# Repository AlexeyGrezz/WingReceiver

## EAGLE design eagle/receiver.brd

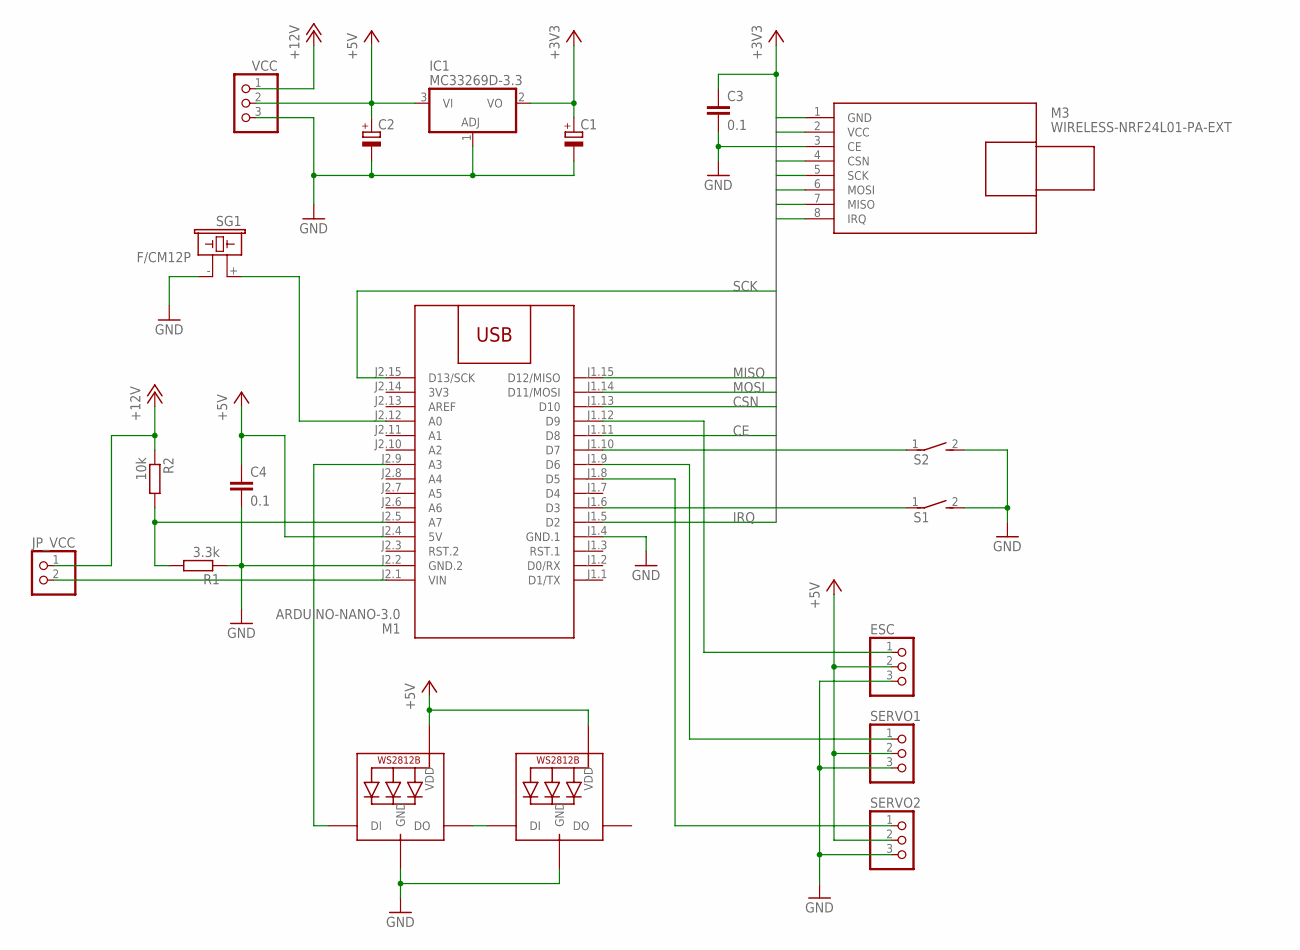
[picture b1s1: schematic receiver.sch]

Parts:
C1, C2: CPOL-EUE3.5-8; E3,5-8
C3, C4: 0.1; C050-024X044
ESC: PINHD-1X3; 1X03
IC1: MC33269D-3.3; DPACK
JP_VCC: PINHD-1X2; 1X02
LED1, LED2: WS2812B_5050N; WS2812B-NARROW
M1: ARDUINO-NANO-3.0
M3: WIRELESS-NRF24L01-PA-EXT; WIRELESS-NRD24L01-PA-EXT
R1: 3.3k; 0207/10
R2: 10k; 0207/10
S1, S2: DS01E; DS-01
SERVO1, SERVO2: PINHD-1X3; 1X03
SG1: F/CM12P
VCC: PINHD-1X3; 1X03

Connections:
3V3: M1.J2.14 (3V3)
+3V3: C1.+, C3.1, IC1.2 (VO), M3.2 (VCC)
+5V: C2.+, C4.1, ESC.2, IC1.3 (VI), LED1.1-VDD (VDD), LED2.1-VDD (VDD), M1.J2.4 (5V), SERVO1.2, SERVO2.2, VCC.2
+12V: JP_VCC.1, R2.1, VCC.1
CE: M1.J1.11 (D8), M3.3 (CE)
CSN: M1.J1.13 (D10), M3.4 (CSN)
GND: C1.-, C2.-, C3.2, C4.2, ESC.3, IC1.1 (ADJ), LED1.3-GND (GND), LED2.3-GND (GND), M1.J1.4 (GND.1), M1.J2.2 (GND.2), M3.1 (GND), R1.1, S1.2, S2.2, SERVO1.3, SERVO2.3, SG1.- (2), VCC.3
IRQ: M1.J1.5 (D2), M3.8 (IRQ)
MISO: M1.J1.15 (D12/MISO), M3.7 (MISO)
MOSI: M1.J1.14 (D11/MOSI), M3.6 (MOSI)
unnamed: ESC.1, M1.J1.12 (D9)
unnamed: M1.J1.9 (D6), SERVO1.1
unnamed: M1.J1.8 (D5), SERVO2.1
unnamed: JP_VCC.2, M1.J2.1 (VIN)
unnamed: M1.J2.5 (A7), R1.2, R2.2
unnamed: LED1.2-DOUT (DO), LED2.4-DIN (DI)
unnamed: M1.J2.12 (A0), SG1.+ (1)
unnamed: LED1.4-DIN (DI), M1.J2.9 (A3)
unnamed: M1.J1.6 (D3), S1.1
unnamed: M1.J1.10 (D7), S2.1
SCK: M1.J2.15 (D13/SCK), M3.5 (SCK)

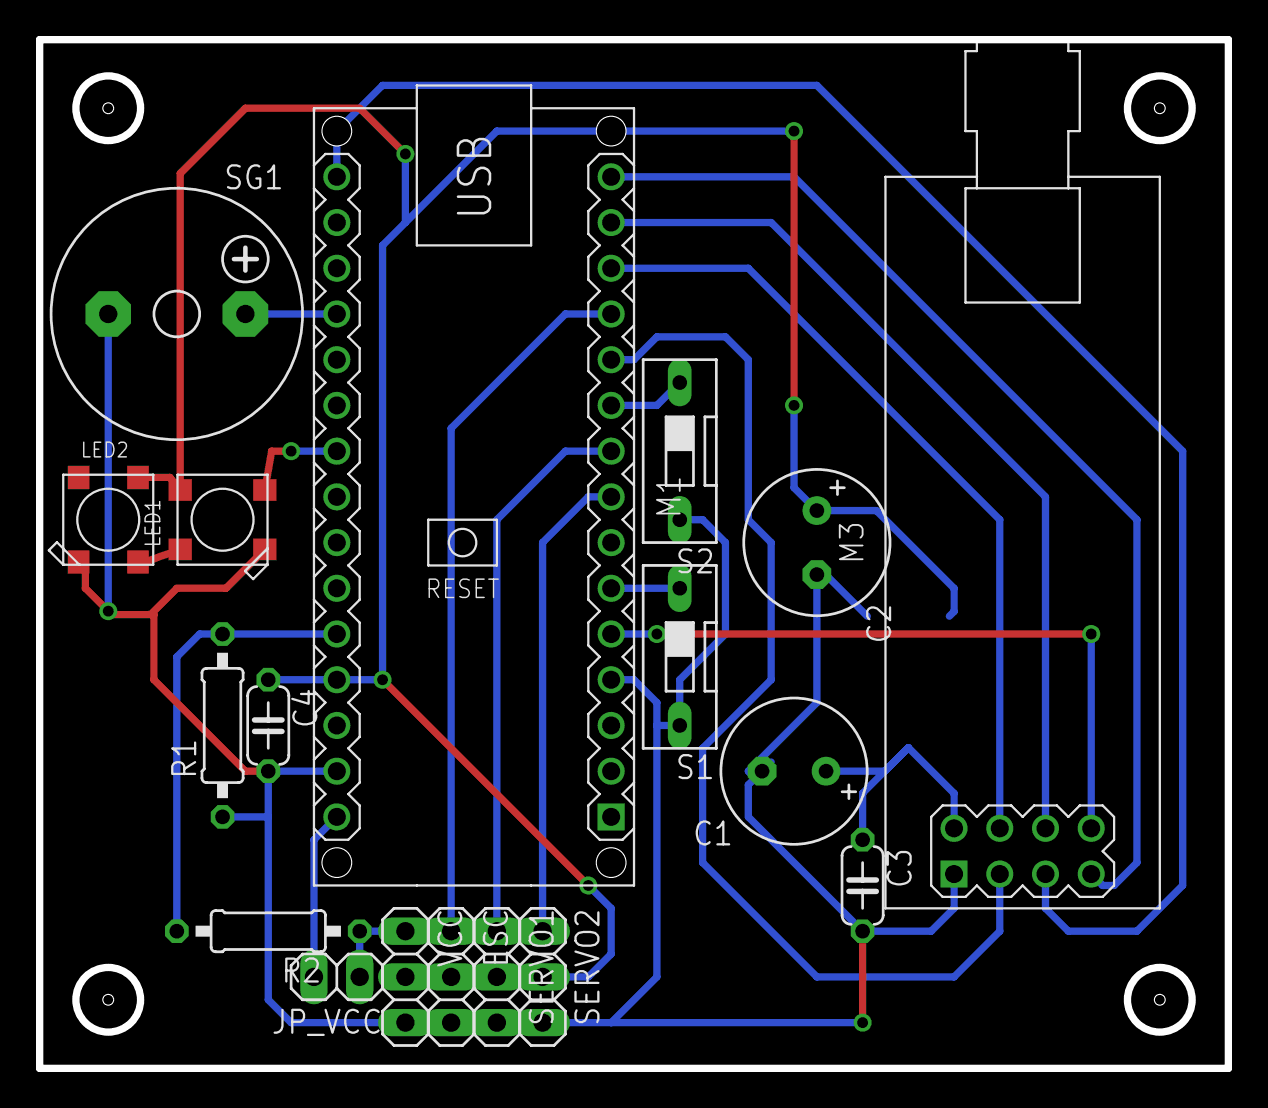
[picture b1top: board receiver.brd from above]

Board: 2 copper layers, 66.0 x 57.2 mm, 19 parts (1 on the bottom side), 20 nets.

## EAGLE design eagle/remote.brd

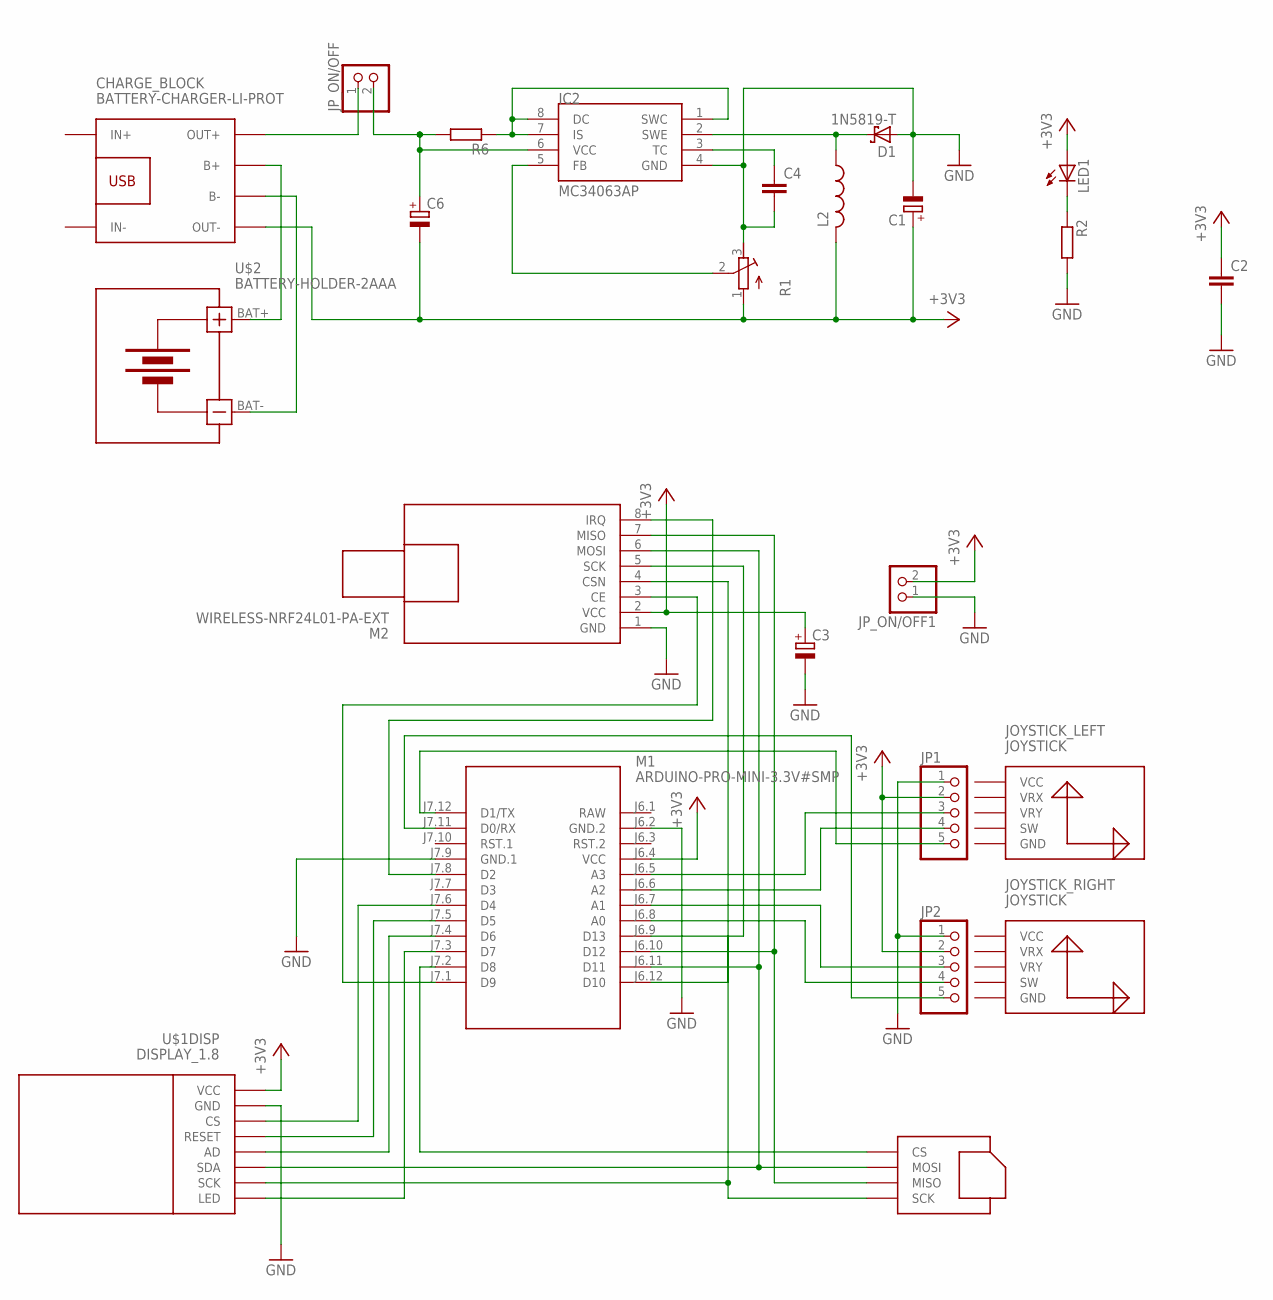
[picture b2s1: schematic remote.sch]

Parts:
C1, C3, C6: CPOL-EUE5-8.5; E5-8,5
C2: C7.5/3; C7.5B3
C4: C5/3.5; C5B3.5
CHARGE_BLOCK: BATTERY-CHARGER-LI-PROT
D1: 1N5819-T; DO41-7.6
IC2: MC34063AP; DIL08
JOYSTICK_LEFT: JOYSTICK
JOYSTICK_RIGHT: JOYSTICK
JP1, JP2: PINHD-1X5; 1X05
JP_ON/OFF, JP_ON/OFF1: PINHD-1X2; 1X02
L2: L-US6000-XXX-RC; 6000-XXXX-RC
LED1: LED5MM
M1: ARDUINO-PRO-MINI-3.3V#SMP; ARDUINO-PRO-MINI#SMP
M2: WIRELESS-NRF24L01-PA-EXT; WIRELESS-NRD24L01-PA-EXT
R1: R-TRIMM3296W; RTRIM3296W
R2: R-EU_0207/10; 0207/10
R6: R-EU_0309/10; 0309/10
U$1: DISPLAY_1.8
U$2: BATTERY-HOLDER-2AAA

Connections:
+3V3: C1.+, C2.1, C3.+, C6.-, CHARGE_BLOCK.OUT-, JP1.2, JP2.2, JP_ON/OFF1.2, L2.2, LED1.A, M1.J6.4 (VCC), M2.2 (VCC), R1.1 (A), U$1.VCC
GND: C1.-, C2.2, C3.-, C4.2, D1.A, IC2.4 (GND), JP1.1, JP2.1, JP_ON/OFF1.1, M1.J6.2 (GND.2), M1.J7.9 (GND.1), M2.1 (GND), R1.3 (E), R2.2, U$1.GND
unnamed: CHARGE_BLOCK.B-, U$2.BAT-
unnamed: CHARGE_BLOCK.B+, U$2.BAT+
unnamed: M1.J7.1 (D9), M2.3 (CE)
unnamed: M1.J6.12 (D10), M2.4 (CSN)
unnamed: M1.J6.9 (D13), M2.5 (SCK), U$1.SCK, U$1.SD_SCK (SCK)
unnamed: M1.J6.11 (D11), M2.6 (MOSI), U$1.SDA, U$1.SD_MOSI (MOSI)
unnamed: M1.J6.10 (D12), M2.7 (MISO), U$1.SD_MISO (MISO)
unnamed: M1.J7.8 (D2), M2.8 (IRQ)
unnamed: M1.J7.6 (D4), U$1.CS
unnamed: M1.J7.4 (D6), U$1.A0 (AD)
unnamed: JP1.4, M1.J6.6 (A2)
unnamed: JP1.3, M1.J6.5 (A3)
unnamed: JP2.3, M1.J6.7 (A1)
unnamed: M1.J7.5 (D5), U$1.RESET
unnamed: M1.J7.3 (D7), U$1.LED
unnamed: JP1.5, M1.J7.12 (D1/TX)
unnamed: JP2.5, M1.J7.11 (D0/RX)
unnamed: JP2.4, M1.J6.8 (A0)
unnamed: C6.+, IC2.6 (VCC), JP_ON/OFF.2, R6.2
unnamed: M1.J7.2 (D8), U$1.SD_CS (CS)
unnamed: IC2.1 (SWC), IC2.7 (IS), IC2.8 (DC), R6.1
unnamed: LED1.K (C), R2.1
unnamed: CHARGE_BLOCK.OUT+, JP_ON/OFF.1
unnamed: IC2.5 (FB), R1.2 (S)
unnamed: D1.C, IC2.2 (SWE), L2.1
unnamed: C4.1, IC2.3 (TC)
RAW: M1.J6.1 (RAW)

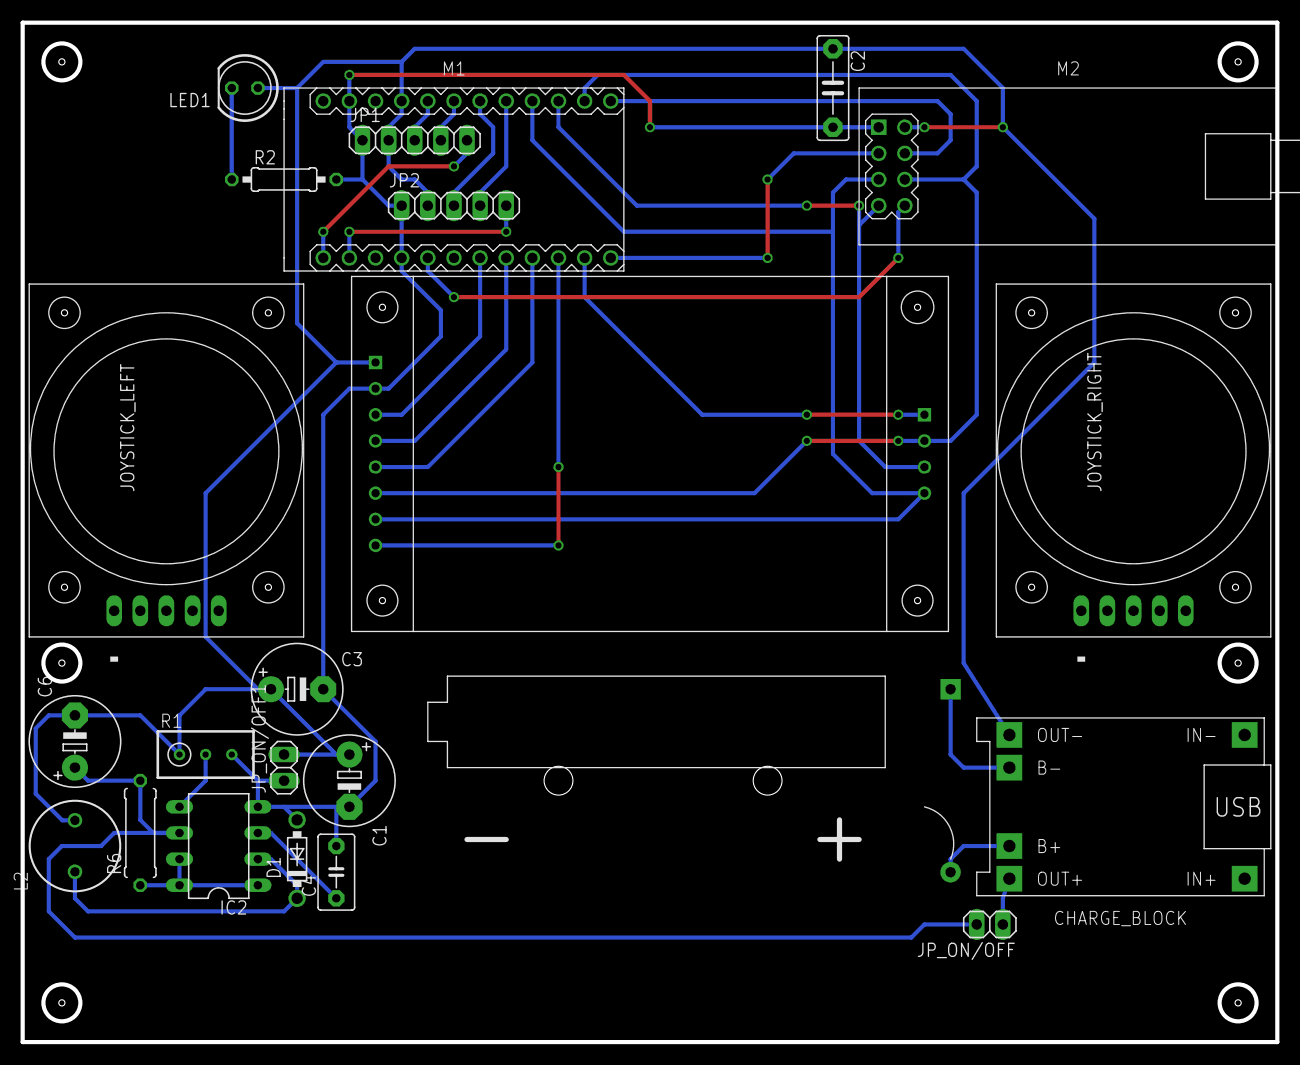
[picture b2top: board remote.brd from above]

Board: 2 copper layers, 121.9 x 99.1 mm, 23 parts (1 on the bottom side), 28 nets.

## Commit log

2018-04-07 inti

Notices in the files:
parts and their libraries:
diy-modules: Released under the Creative Commons Attribution 4.0 International License: http://creativecommons.org/licenses/by/4.0
